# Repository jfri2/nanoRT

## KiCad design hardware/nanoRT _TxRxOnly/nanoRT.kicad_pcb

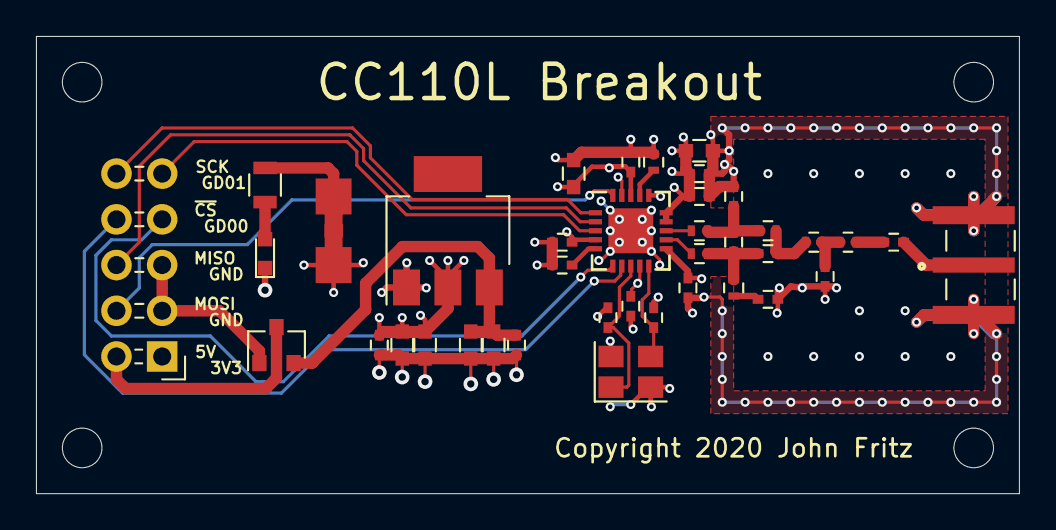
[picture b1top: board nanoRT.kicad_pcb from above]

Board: 4 copper layers, 54.6 x 25.4 mm, 43 parts (0 on the bottom side), 25 nets.

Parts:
C1, C5, C6, C8, C10, C11, C13, C22, C23: 0.1uF; C_0402
C2, C4: 20pF; C_0402
C3, C7, C9, C16, C17, C19: 2.2uF; C_0603
C12: 1pF; C_0402
C14, C18: 1.5pF; C_0402
C15, C21: 100pF; C_0402
C20: 3.3pF; C_0402
D2: POWER; LED_0603
H1, H2, H3, H4: MountingHole; MountingHole_2.2mm_M2
J2: CONN; Pin_Header_Angled_2x05_Pitch2.54mm
J5: SMA; TAOGLAS_EMPCB.SMAFSTJ.B.HT
JP1: PWR_LED; NetTie-I_Connected_SMD
L1, L2, L5, L6: 12nH; L_0402
L3, L4: 18nH; L_0402
Q1: AO3401A; SOT-23
R2: 56k; R_0402
R3: 510; R_0805
U1: CC110L; QFN-20-1EP_4x4mm_Pitch0.5mm
U2: AMS1117-3.3; SOT-223
Y1: TSX-3225_27MHz; Crystal_SMD_3225-4pin_3.2x2.5mm

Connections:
+3V3: C3.1, C5.1, C6.1, C8.1, C10.1, C11.1, C13.1, C16.1, C17.1, C19.1, C23.1, J2.1, JP1.2, U1.4, U1.9, U1.11, U1.14, U1.15, U1.18, U2.2
/5V_EXT: J2.2, Q1.3
/5V_PROT: C7.1, C9.1, C22.1, Q1.2, U2.3
/DCOUPL: C1.1, U1.5
/GDO0: J2.7, U1.6
/GDO1: J2.9, U1.3
/RBIAS: R2.1, U1.17
/RF_N: L1.1, U1.13
/RF_P: L2.1, U1.12
/SPI2_MISO: J2.6, U1.2
/SPI2_MOSI: J2.4, U1.20
/SPI2_SCK: J2.10, U1.1
/SPI2_~CS: J2.8, U1.7
/XTAL_Q1: C2.1, U1.8, Y1.1
/XTAL_Q2: C4.1, U1.10, Y1.3
GND: C1.2, C2.2, C3.2, C4.2, C5.2, C6.2, C7.2, C8.2, C9.2, C10.2, C11.2, C13.2, C14.1, C15.2, C16.2, C17.2, C19.2, C20.2, C22.2, C23.2, D2.1, J2.3, J2.5, J5.2, Q1.1, R2.2, U1.16, U1.19, U1.21, U2.1, Y1.2, Y1.4
unnamed: C12.1, C14.2, L1.2, L4.1
unnamed: C12.2, C18.2, L2.2, L3.1
unnamed: C15.1, L3.2
unnamed: C18.1, L4.2, L5.1
unnamed: C20.1, L5.2, L6.1
unnamed: C21.1, J5.1
unnamed: C21.2, L6.2
unnamed: D2.2, R3.2
unnamed: JP1.1, R3.1

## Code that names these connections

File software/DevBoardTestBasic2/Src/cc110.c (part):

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        // Packet

        // Default GDO2 and GDO1 Config
#define SMARTRF_SETTING_IOCFG0          0x06    // 0x06 for GDO0 config
        // 0xD391 Sync word
        // Packet len of 255 (changed later)
        // CRC autoflush disabled; append status enabled,
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    // De-init SPI, set SCK output, 1; MOSI output, 0; MISO input
    HAL_SPI_MspDeInit(&hspi2);

    GPIO_InitStruct.Pin = SPI2_SCK_Pin;
    GPIO_InitStruct.Mode = GPIO_MODE_OUTPUT_PP;
    GPIO_InitStruct.Pull = GPIO_NOPULL;
    GPIO_InitStruct.Speed = GPIO_SPEED_FREQ_LOW;
    HAL_GPIO_Init(SPI2_SCK_Port, &GPIO_InitStruct);

    GPIO_InitStruct.Pin = SPI2_MOSI_Pin;
    GPIO_InitStruct.Mode = GPIO_MODE_OUTPUT_PP;
    GPIO_InitStruct.Pull = GPIO_NOPULL;
    GPIO_InitStruct.Speed = GPIO_SPEED_FREQ_LOW;
    HAL_GPIO_Init(SPI2_MOSI_Port, &GPIO_InitStruct);

    GPIO_InitStruct.Pin = SPI2_MISO_Pin;
    GPIO_InitStruct.Mode = GPIO_MODE_INPUT;
    GPIO_InitStruct.Pull = GPIO_PULLUP;
    HAL_GPIO_Init(SPI2_MISO_Port, &GPIO_InitStruct);

    HAL_GPIO_WritePin(SPI2_SCK_Port, SPI2_SCK_Pin, GPIO_PIN_SET);
    HAL_Delay(1);
    HAL_GPIO_WritePin(SPI2_MOSI_Port, SPI2_MOSI_Pin, GPIO_PIN_RESET);

    // Strobe CSn Low/High, Hold CSn High for min 40 usec
    HAL_GPIO_WritePin(SPI2_NSS_GPIO_Port, SPI2_NSS_Pin, GPIO_PIN_RESET);
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
    // Pull CSn Low and wait for MISO to go low
    HAL_GPIO_WritePin(SPI2_NSS_GPIO_Port, SPI2_NSS_Pin, GPIO_PIN_RESET);
    while ((HAL_GPIO_ReadPin(SPI2_MISO_Port, SPI2_MISO_Pin) != GPIO_PIN_RESET)
            && (timeMs < timeoutMs))
    {
        HAL_Delay(1);
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
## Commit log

2020-08-02 Initial commit - Tx/Rx Only
2020-08-22 Fixed logger, added low level functions for radio control and test
2020-08-23 more attempts to get tx/rx working
2020-09-15 Completed and verified demo of CC110L Tx/Rx between two STM32 dev boards and two CC110L dev boards

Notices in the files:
hardware/nanoRT _TxRxOnly/nanoRT.kicad_pcb:
Copyright 2020 John Fritz
software/DevBoardTestBasic2/Src/cc110.c:
(C) COPYRIGHT John Fritz *****END OF FILE
